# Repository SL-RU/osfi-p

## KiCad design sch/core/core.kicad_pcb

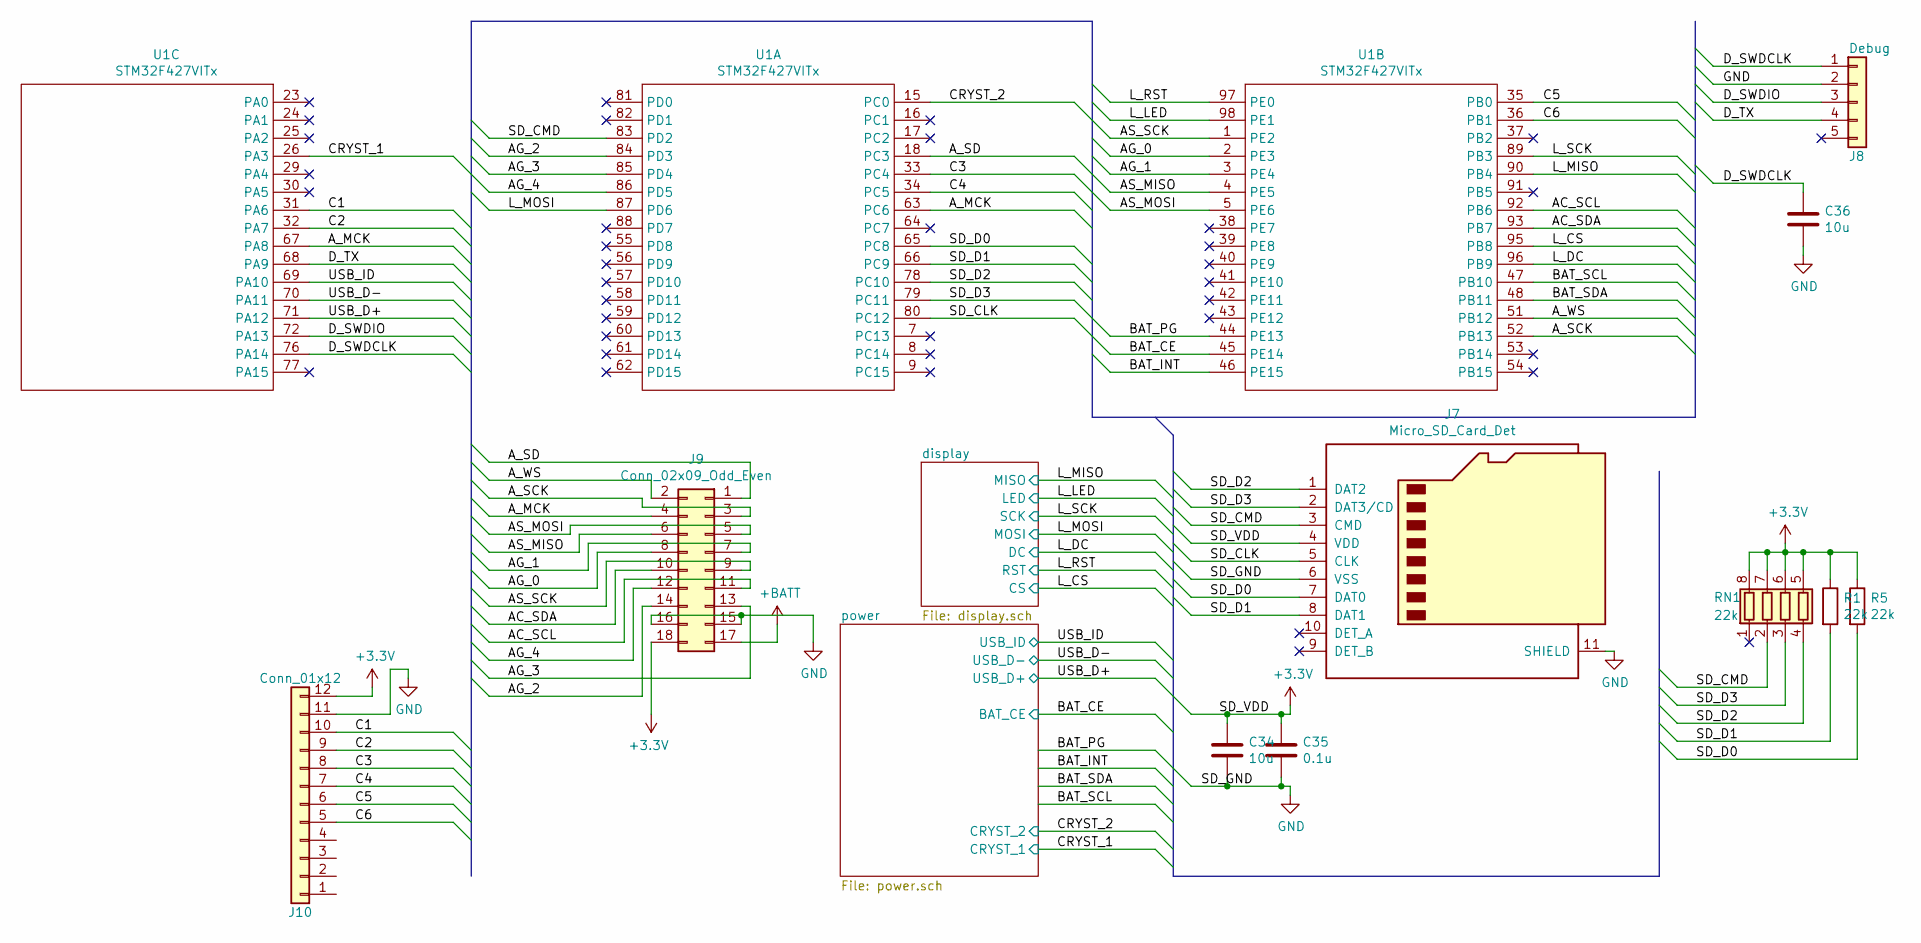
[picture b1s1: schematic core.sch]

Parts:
C34, C36: 10u; C_0805_2012Metric
C35: 0.1u; C_0402
J7: Micro_SD_Card_Det; microSD_Card_Receptacle_Hirose_DM3AT-SF-PEJM5
J8: Debug; PinHeader_1x05_P1.27mm_Vertical
J9: Conn_02x09_Odd_Even; PinSocket_2x09_P2.54mm_Vertical
J10: Conn_01x12; conn_1_12
R1: 22k; R_0603_1608Metric_Pad1.05x0.95mm_HandSolder
R5: 22k; R_0603_HandSoldering
RN1: 22k; R_Array_Concave_4x0603
U1: STM32F427VITx; LQFP-100_14x14mm_Pitch0.5mm

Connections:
+3V3: C34.1, C35.1, J7.4 (VDD), J9.18, J10.12, R1.1, R5.1, RN1.5 (R4.2), RN1.6 (R3.2), RN1.7 (R2.2), RN1.8 (R1.2); also elsewhere on the board
+BATT: J9.17; also elsewhere on the board
/AC_SCL: J9.11, U1.92 (PB6)
/AC_SDA: J9.10, U1.93 (PB7)
/AG_0: J9.8, U1.2 (PE3)
/AG_1: J9.7, U1.3 (PE4)
/AG_2: J9.14, U1.84 (PD3)
/AG_3: J9.13, U1.85 (PD4)
/AG_4: J9.12, U1.86 (PD5)
/AS_MISO: J9.6, U1.4 (PE5)
/AS_MOSI: J9.5, U1.5 (PE6)
/AS_SCK: J9.9, U1.1 (PE2)
/A_MCK: J9.4, U1.63 (PC6), U1.67 (PA8)
/A_SCK: J9.3, U1.52 (PB13)
/A_SD: J9.1, U1.18 (PC3)
/A_WS: J9.2, U1.51 (PB12)
/BAT_CE: U1.45 (PE14); also elsewhere on the board
/BAT_INT: U1.46 (PE15)
/BAT_PG: U1.44 (PE13)
/BAT_SCL: U1.47 (PB10)
/BAT_SDA: U1.48 (PB11)
/C1: J10.10, U1.31 (PA6)
/C2: J10.9, U1.32 (PA7)
/C3: J10.8, U1.33 (PC4)
/C4: J10.7, U1.34 (PC5)
/C5: J10.6, U1.35 (PB0)
/C6: J10.5, U1.36 (PB1)
/CRYST_1: U1.26 (PA3); also elsewhere on the board
/CRYST_2: U1.15 (PC0); also elsewhere on the board
/D_SWDCLK: C36.1, J8.1, U1.76 (PA14)
/D_SWDIO: J8.3, U1.72 (PA13)
/D_TX: J8.4, U1.68 (PA9)
/L_CS: U1.95 (PB8); also elsewhere on the board
/L_DC: U1.96 (PB9); also elsewhere on the board
/L_LED: U1.98 (PE1); also elsewhere on the board
/L_MISO: U1.90 (PB4); also elsewhere on the board
/L_MOSI: U1.87 (PD6); also elsewhere on the board
/L_RST: U1.97 (PE0); also elsewhere on the board
/L_SCK: U1.89 (PB3); also elsewhere on the board
/SD_CLK: J7.5 (CLK), U1.80 (PC12)
/SD_CMD: J7.3 (CMD), RN1.2 (R2.1), U1.83 (PD2)
/SD_D0: J7.7 (DAT0), R5.2, U1.65 (PC8)
/SD_D1: J7.8 (DAT1), R1.2, U1.66 (PC9)
/SD_D2: J7.1 (DAT2), RN1.4 (R4.1), U1.78 (PC10)
/SD_D3: J7.2 (DAT3/CD), RN1.3 (R3.1), U1.79 (PC11)
/USB_D+: U1.71 (PA12); also elsewhere on the board
/USB_D-: U1.70 (PA11); also elsewhere on the board
/USB_ID: U1.69 (PA10); also elsewhere on the board
GND: C34.2, C35.2, C36.2, J7.6 (VSS), J7.11 (SHIELD), J8.2, J9.15, J9.16, J10.11; also elsewhere on the board

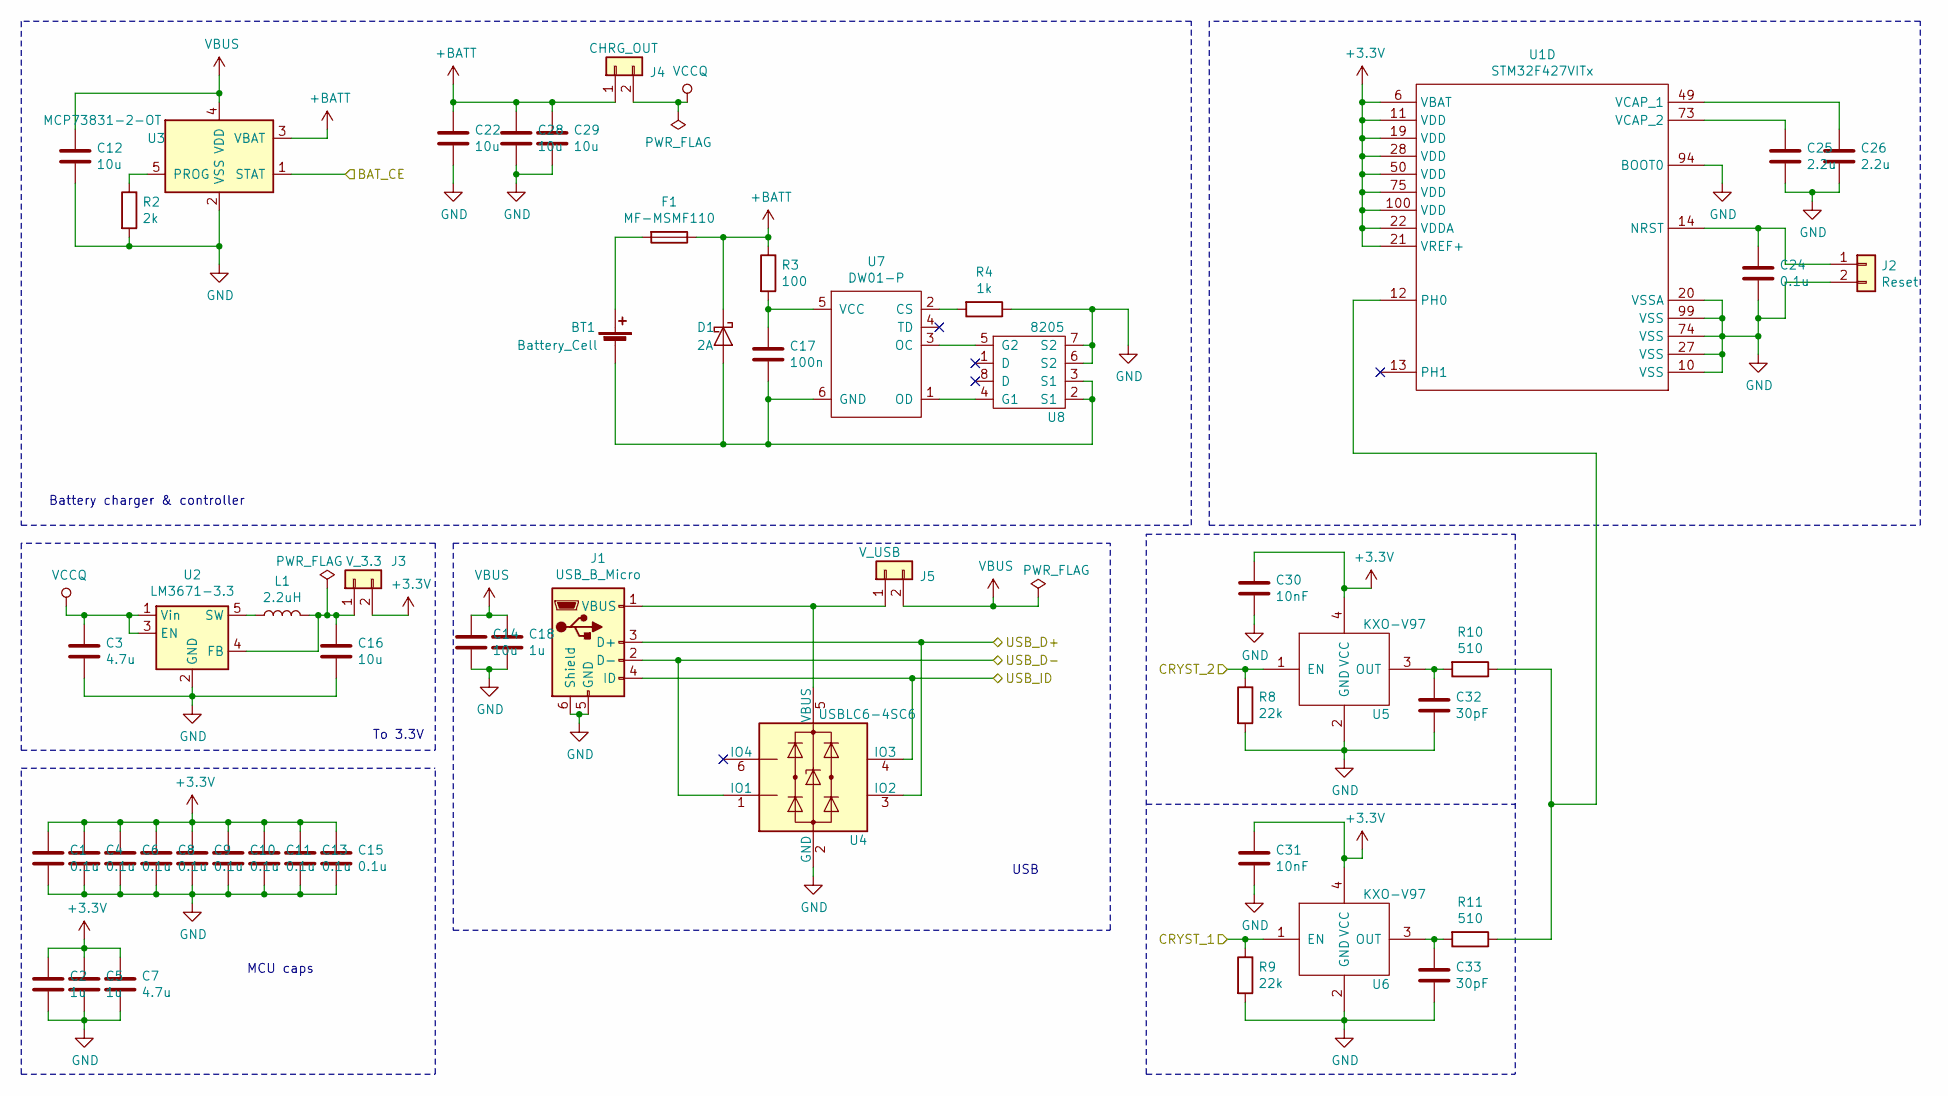
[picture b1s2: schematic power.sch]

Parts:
BT1: Battery_Cell; PinSocket_1x02_P2.54mm_Vertical
C1, C4, C6, C8, C9, C10, C11, C13, C15, C24: 0.1u; C_0402_NoSilk
C2, C5, C18: 1u; C_0805_2012Metric
C3, C7: 4.7u; C_0805_2012Metric
C12, C14, C16, C22, C28, C29: 10u; C_0805_2012Metric
C17: 100n; C_0805_2012Metric
C25, C26: 2.2u; C_0805_2012Metric
C30, C31: 10nF; C_0805_2012Metric
C32, C33: 30pF; C_0805_2012Metric
D1: 2A; D_2010_5025Metric
F1: MF-MSMF110; Fuse_1812_4532Metric_Pad1.30x3.40mm_HandSolder
J1: USB_B_Micro; USB_Micro-B
J2: Reset; PinHeader_1x02_P1.27mm_Vertical
J3: V_3.3; PinHeader_1x02_P2.54mm_Vertical
J4: CHRG_OUT; PinHeader_1x02_P2.54mm_Vertical
J5: V_USB; PinHeader_1x02_P2.54mm_Vertical
L1: 2.2uH; L_1210_HandSoldering
R2: 2k; R_0603_1608Metric_Pad1.05x0.95mm_HandSolder
R3: 100; R_0603_1608Metric_Pad1.05x0.95mm_HandSolder
R4: 1k; R_0603_1608Metric_Pad1.05x0.95mm_HandSolder
R8, R9: 22k; R_0603
R10, R11: 510; R_0603
U1: STM32F427VITx; LQFP-100_14x14mm_Pitch0.5mm
U2: LM3671-3.3; TSOT-23-5
U3: MCP73831-2-OT; SOT-23-5
U4: USBLC6-4SC6; SOT-23-6
U5, U6: KXO-V97; Crystal_SMD_7050-4pin_7.0x5.0mm
U7: DW01-P; SOT-23-6
U8: 8205; TSSOP-8_4.4x3mm_P0.65mm

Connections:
+3V3: C1.1, C2.1, C4.1, C5.1, C6.1, C7.1, C8.1, C9.1, C10.1, C11.1, C13.1, C15.1, C30.1, C31.1, J3.2, U1.6 (VBAT), U1.11 (VDD), U1.19 (VDD), U1.21 (VREF+), U1.22 (VDDA), U1.28 (VDD), U1.50 (VDD), U1.75 (VDD), U1.100 (VDD), U5.4 (VCC), U6.4 (VCC); also elsewhere on the board
+BATT: C22.1, C28.1, C29.1, D1.1 (K), F1.1, J4.1, R3.1, U3.3 (VBAT); also elsewhere on the board
/BAT_CE: U3.1 (STAT); also elsewhere on the board
/CRYST_1: R9.1, U6.1 (EN); also elsewhere on the board
/CRYST_2: R8.1, U5.1 (EN); also elsewhere on the board
/USB_D+: J1.3 (D+), U4.3 (IO2); also elsewhere on the board
/USB_D-: J1.2 (D-), U4.1 (IO1); also elsewhere on the board
/USB_ID: J1.4 (ID), U4.4 (IO3); also elsewhere on the board
GND: C1.2, C2.2, C3.2, C4.2, C5.2, C6.2, C7.2, C8.2, C9.2, C10.2, C11.2, C12.2, C13.2, C14.2, C15.2, C16.2, C18.2, C22.2, C24.2, C25.1, C26.1, C28.2, C29.2, C30.2, C31.2, C32.2, C33.2, J1.5 (GND), J1.6 (Shield), J2.2, R2.2, R4.1, R8.2, R9.2, U1.10 (VSS), U1.20 (VSSA), U1.27 (VSS), U1.74 (VSS), U1.94 (BOOT0), U1.99 (VSS), U2.2 (GND), U3.2 (VSS), U4.2 (GND), U5.2 (GND), U6.2 (GND), U8.6 (S2), U8.7 (S2); also elsewhere on the board
unnamed: BT1.1 (+), F1.2
unnamed: BT1.2 (-), C17.2, D1.2 (A), U7.6 (GND), U8.2 (S1), U8.3 (S1)
unnamed: C16.1, J3.1, L1.2, U2.4 (FB)
unnamed: C17.1, R3.2, U7.5 (VCC)
unnamed: C24.1, J2.1, U1.14 (NRST)
unnamed: C25.2, U1.73 (VCAP_2)
unnamed: C26.2, U1.49 (VCAP_1)
unnamed: C32.1, R10.2, U5.3 (OUT)
unnamed: C33.1, R11.2, U6.3 (OUT)
unnamed: J1.1 (VBUS), J5.1, U4.5 (VBUS)
unnamed: L1.1, U2.5 (SW)
unnamed: R2.1, U3.5 (PROG)
unnamed: R4.2, U7.2 (CS)
unnamed: R10.1, R11.1, U1.12 (PH0)
unnamed: U7.1 (OD), U8.4 (G1)
unnamed: U7.3 (OC), U8.5 (G2)
VBUS: C12.1, C14.1, C18.1, J5.2, U3.4 (VDD)
VCCQ: C3.1, J4.2, U2.1 (Vin), U2.3 (EN)

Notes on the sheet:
To 3.3V
Battery charger & controller
MCU caps
USB

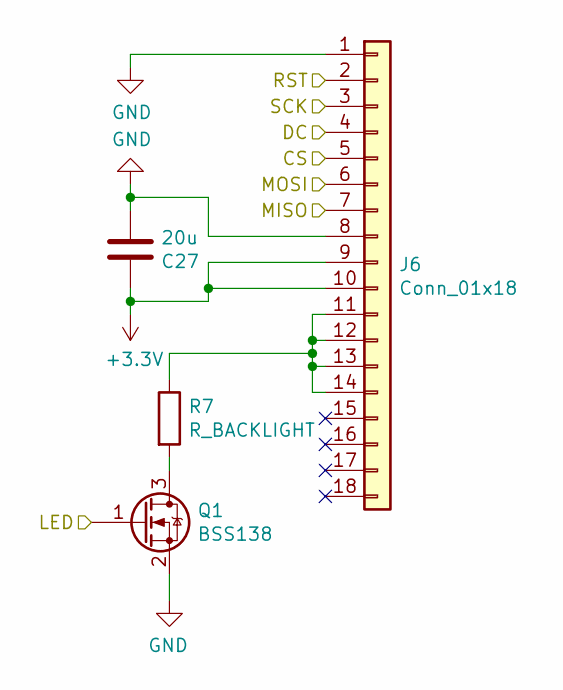
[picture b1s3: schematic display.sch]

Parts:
C27: 20u; C_0805_2012Metric
J6: Conn_01x18; ILI9341_18Pin
Q1: BSS138; SOT-23
R7: R_BACKLIGHT; R_0805

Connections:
+3V3: C27.1, J6.9, J6.10; also elsewhere on the board
/L_CS: J6.5; also elsewhere on the board
/L_DC: J6.4; also elsewhere on the board
/L_LED: Q1.1 (G); also elsewhere on the board
/L_MISO: J6.7; also elsewhere on the board
/L_MOSI: J6.6; also elsewhere on the board
/L_RST: J6.2; also elsewhere on the board
/L_SCK: J6.3; also elsewhere on the board
GND: C27.2, J6.1, J6.8, Q1.2 (S); also elsewhere on the board
unnamed: J6.11, J6.12, J6.13, J6.14, R7.1
unnamed: Q1.3 (D), R7.2

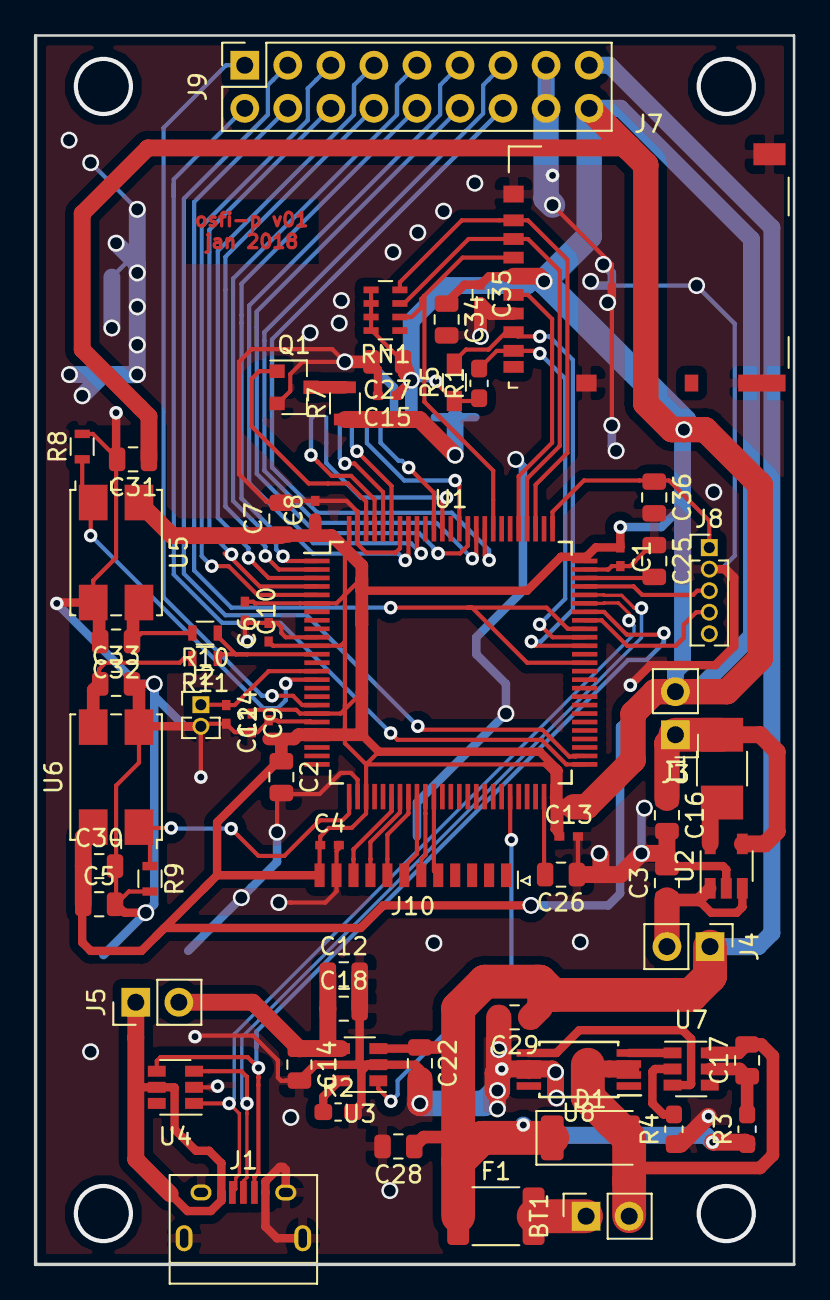
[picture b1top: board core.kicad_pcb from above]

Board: 2 copper layers, 44.8 x 72.5 mm, 66 parts (1 on the bottom side), 65 nets.

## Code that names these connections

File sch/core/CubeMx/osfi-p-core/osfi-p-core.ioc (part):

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Mcu.Name=STM32F427V(G-I)Tx
Mcu.Package=LQFP100
Mcu.UserName=STM32F427VITx
PA10.Signal=USB_OTG_FS_ID
PA11.Mode=Device_Only
PA11.Signal=USB_OTG_FS_DM
PA12.Mode=Device_Only
PA12.Signal=USB_OTG_FS_DP
PA13.Mode=Serial_Wire
PA13.Signal=SYS_JTMS-SWDIO
PA14.Mode=Serial_Wire
PA14.Signal=SYS_JTCK-SWCLK
PA3.GPIOParameters=GPIO_Label
PA3.GPIO_Label=CRYST_1
PA3.Signal=GPIO_Output
PA6.Signal=S_TIM3_CH1
PA7.Signal=S_TIM3_CH2
PA8.Mode=Clock-out-1
PA8.Signal=RCC_MCO_1
PA9.Mode=Half_duplex(single_wire_mode)
PA9.Signal=USART1_TX
PB0.Signal=GPIO_Input
PB1.Signal=GPIO_Input
PB10.GPIOParameters=GPIO_Label
PB10.GPIO_Label=BAT_SCL
PB10.Mode=I2C
PB10.Signal=I2C2_SCL
PB11.GPIOParameters=GPIO_Label
PB11.GPIO_Label=BAT_SDA
PB11.Mode=I2C
PB11.Signal=I2C2_SDA
PB12.GPIOParameters=GPIO_Label
PB12.GPIO_Label=A_WS
PB12.Mode=Half_Duplex_Master
PB12.Signal=I2S2_WS
PB13.GPIOParameters=GPIO_Label
PB13.GPIO_Label=A_SCK
PB13.Mode=Half_Duplex_Master
PB13.Signal=I2S2_CK
PB3.GPIOParameters=GPIO_Label
PB3.GPIO_Label=L_SCK
PB3.Mode=Full_Duplex_Master
PB3.Signal=SPI3_SCK
PB4.GPIOParameters=GPIO_Label
PB4.GPIO_Label=L_MISO
PB4.Mode=Full_Duplex_Master
PB4.Signal=SPI3_MISO
PB6.GPIOParameters=GPIO_Label
PB6.GPIO_Label=AC_SCL
PB6.Mode=I2C
PB6.Signal=I2C1_SCL
PB7.GPIOParameters=GPIO_Label
PB7.GPIO_Label=AC_SDA
PB7.Mode=I2C
PB7.Signal=I2C1_SDA
PB8.GPIOParameters=GPIO_Label
PB8.GPIO_Label=L_CS
PB8.Signal=GPIO_Output
PB9.GPIOParameters=GPIO_Label
PB9.GPIO_Label=L_DC
PB9.Signal=GPIO_Output
PC0.GPIOParameters=GPIO_Label
PC0.GPIO_Label=CRYST_2
PC0.Signal=GPIO_Output
PC10.Mode=SD_4_bits_Wide_bus
PC10.Signal=SDIO_D2
PC11.Mode=SD_4_bits_Wide_bus
PC11.Signal=SDIO_D3
PC12.Mode=SD_4_bits_Wide_bus
PC12.Signal=SDIO_CK
PC3.GPIOParameters=GPIO_Label
PC3.GPIO_Label=A_SD
PC3.Mode=Half_Duplex_Master
PC3.Signal=I2S2_SD
PC4.Signal=GPIO_Input
PC5.Signal=GPIO_Input
PC6.Mode=Master_Clock_Activated
PC6.Signal=I2S2_MCK
PC8.Mode=SD_4_bits_Wide_bus
PC8.Signal=SDIO_D0
PC9.Mode=SD_4_bits_Wide_bus
PC9.Signal=SDIO_D1
PD2.Mode=SD_4_bits_Wide_bus
PD2.Signal=SDIO_CMD
PD3.GPIOParameters=GPIO_Label
PD3.GPIO_Label=AG_2
PD3.Signal=GPIO_Output
PD4.GPIOParameters=GPIO_Label
PD4.GPIO_Label=AG_3
PD4.Signal=GPIO_Output
PD5.GPIOParameters=GPIO_Label
PD5.GPIO_Label=AG_4
PD5.Signal=GPIO_Output
PD6.GPIOParameters=GPIO_Label
PD6.GPIO_Label=L_MOSI
PD6.Mode=Full_Duplex_Master
PD6.Signal=SPI3_MOSI
PE0.GPIOParameters=GPIO_Label
PE0.GPIO_Label=L_RST
PE0.Signal=GPIO_Output
PE1.GPIOParameters=GPIO_Label
PE1.GPIO_Label=L_LED
PE1.Signal=GPIO_Output
PE13.GPIOParameters=GPIO_Label
PE13.GPIO_Label=BAT_INT
PE13.Signal=GPIO_Input
PE14.GPIOParameters=GPIO_Label
PE14.GPIO_Label=BAT_CE
PE14.Signal=GPIO_Output
PE15.GPIOParameters=GPIO_Label
PE15.GPIO_Label=BAT_PG
PE15.Signal=GPXTI15
PE2.GPIOParameters=GPIO_Label
PE2.GPIO_Label=AS_SCK
PE2.Mode=Full_Duplex_Master
PE2.Signal=SPI4_SCK
PE3.GPIOParameters=GPIO_Label
PE3.GPIO_Label=AG_0
PE3.Signal=GPIO_Output
PE4.GPIOParameters=GPIO_Label
PE4.GPIO_Label=AG_1
PE4.Signal=GPIO_Output
PE5.GPIOParameters=GPIO_Label
PE5.GPIO_Label=AS_MISO
PE5.Mode=Full_Duplex_Master
PE5.Signal=SPI4_MISO
PE6.GPIOParameters=GPIO_Label
PE6.GPIO_Label=AS_MOSI
PE6.Mode=Full_Duplex_Master
PE6.Signal=SPI4_MOSI
PH0/OSC_IN.Mode=HSE-External-Clock-Source
PH0/OSC_IN.Signal=RCC_OSC_IN
PH1/OSC_OUT.Mode=HSE-External-Clock-Source
PH1/OSC_OUT.Signal=RCC_OSC_OUT
RCC.HSE_VALUE=25000000
RCC.SYSCLKFreq_VALUE=120000000
RCC.SYSCLKSource=RCC_SYSCLKSOURCE_PLLCLK
board=custom

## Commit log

2019-01-14 first
2019-01-16 sch wip
2019-01-21 sch core done
2019-01-21 save
2019-03-07 makise gui add
2019-03-07 makise gui submodule
2019-03-08 FCKNG SD CARD
2019-03-12 HardFault
2019-03-13 makise driver fix
2019-03-19 sch upd
2019-03-20 new charger schematic
2019-03-23 l6470
2019-03-23 pcb upd
2019-03-24 PCB v.2 completed
